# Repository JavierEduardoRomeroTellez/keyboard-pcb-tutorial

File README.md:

# keyboard-pcb-tutorial
Trying to make a keyboard PCB

I followed the guide of ai03, can find in the following link https://wiki.ai03.com/books/pcb-design/chapter/pcb-designer-guide

Here some screenshots

Schema:

PCB Routing:

3D view:

Note: In the KiCad rules check it throws me some errors but are about the footprints so i decided to ignore they, i dont really know if the PCB works

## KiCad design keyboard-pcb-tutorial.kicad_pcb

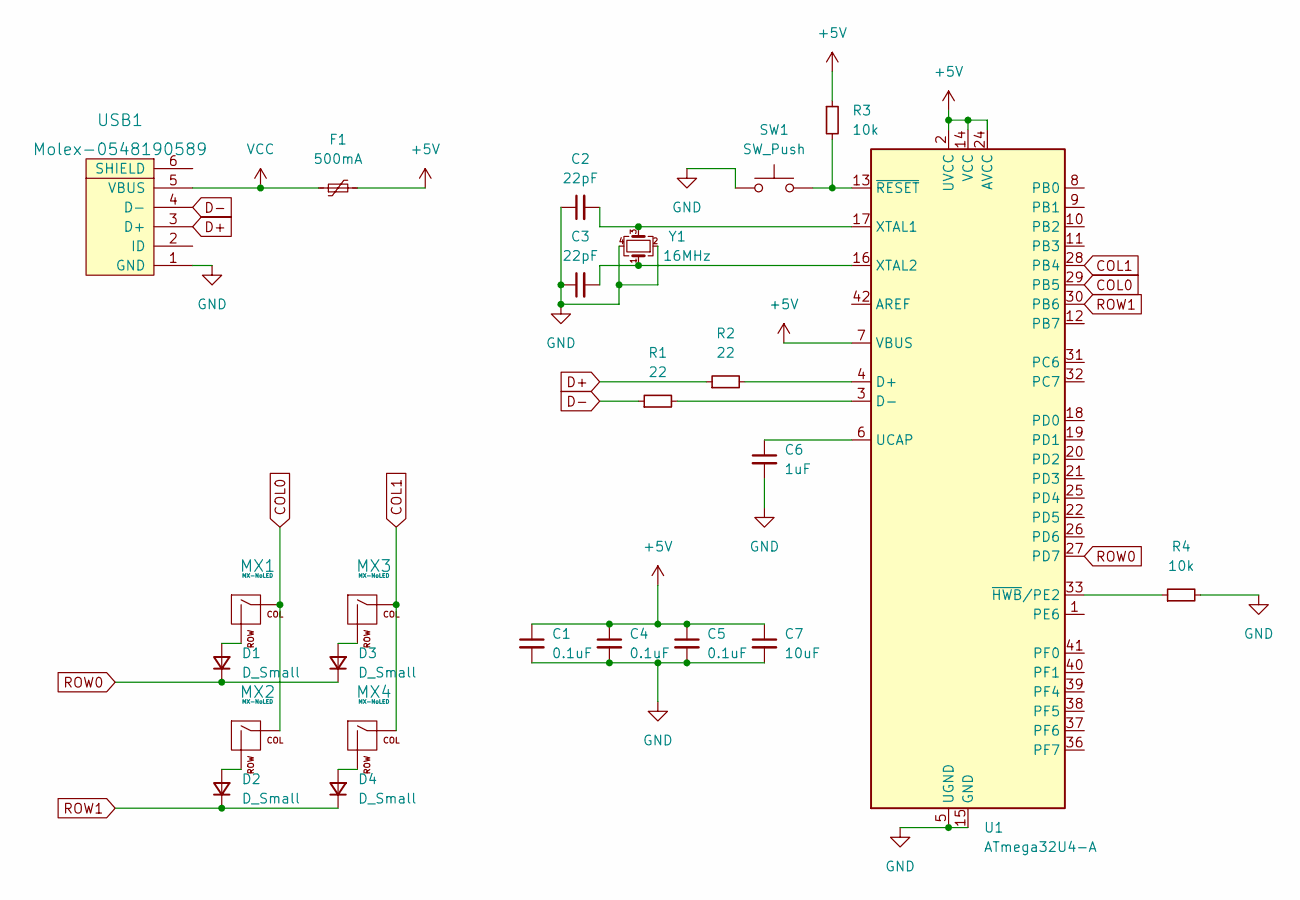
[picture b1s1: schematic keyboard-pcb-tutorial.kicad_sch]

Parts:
C1, C4, C5: 0.1uF; C_0805_2012Metric
C2, C3: 22pF; C_0805_2012Metric
C6: 1uF; C_0805_2012Metric
C7: 10uF; C_0805_2012Metric
D1, D2, D3, D4: D_Small; D_SOD-123
F1: 500mA; Fuse_1206_3216Metric
MX1, MX2, MX3, MX4: MX-NoLED; MX-1U-NoLED
R1, R2: 22; R_0805_2012Metric
R3, R4: 10k; R_0805_2012Metric
SW1: SW_Push; SKQG-1155865
U1: ATmega32U4-A; TQFP-44_10x10mm_P0.8mm
USB1: Molex-0548190589
Y1: 16MHz; Crystal_SMD_3225-4Pin_3.2x2.5mm

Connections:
+5V: C1.1, C4.1, C5.1, C7.1, F1.2, R3.1, U1.2 (UVCC), U1.7 (VBUS), U1.14 (VCC), U1.24 (AVCC), U1.34 (VCC), U1.44 (AVCC)
COL0: MX1.1 (COL), MX2.1 (COL), U1.29 (PB5)
COL1: MX3.1 (COL), MX4.1 (COL), U1.28 (PB4)
D+: R2.1, USB1.3 (D+)
D-: R1.1, USB1.4 (D-)
GND: C1.2, C2.1, C3.1, C4.2, C5.2, C6.2, C7.2, R4.2, SW1.1, U1.5 (UGND), U1.15 (GND), U1.23 (GND), U1.35 (GND), U1.43 (GND), USB1.1 (GND), Y1.2, Y1.4
unnamed: C2.2, U1.17 (XTAL1), Y1.3
unnamed: C3.2, U1.16 (XTAL2), Y1.1
unnamed: C6.1, U1.6 (UCAP)
unnamed: D1.2 (A), MX1.2 (ROW)
unnamed: D2.2 (A), MX2.2 (ROW)
unnamed: D3.2 (A), MX3.2 (ROW)
unnamed: D4.2 (A), MX4.2 (ROW)
unnamed: R1.2, U1.3 (D-)
unnamed: R2.2, U1.4 (D+)
unnamed: R3.2, SW1.2, U1.13 (~RESET)
unnamed: R4.1, U1.33 (~HWB/PE2)
ROW0: D1.1 (K), D3.1 (K), U1.27 (PD7)
ROW1: D2.1 (K), D4.1 (K), U1.30 (PB6)
VCC: F1.1, USB1.5 (VBUS)

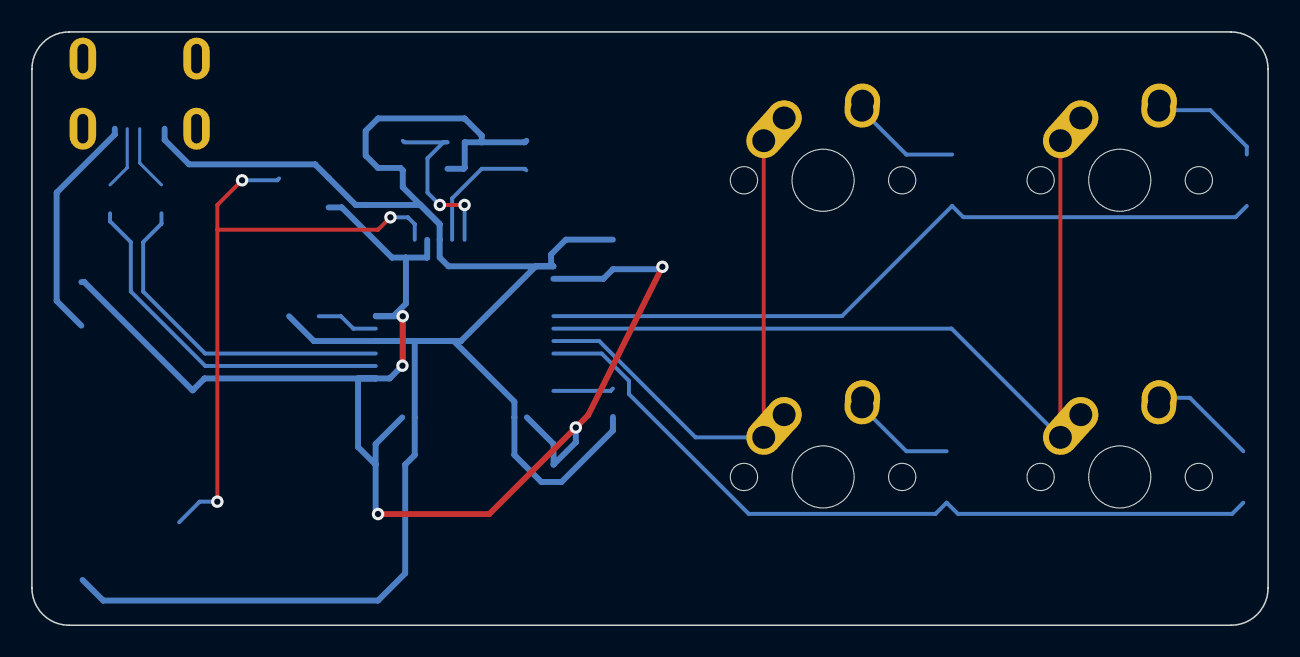
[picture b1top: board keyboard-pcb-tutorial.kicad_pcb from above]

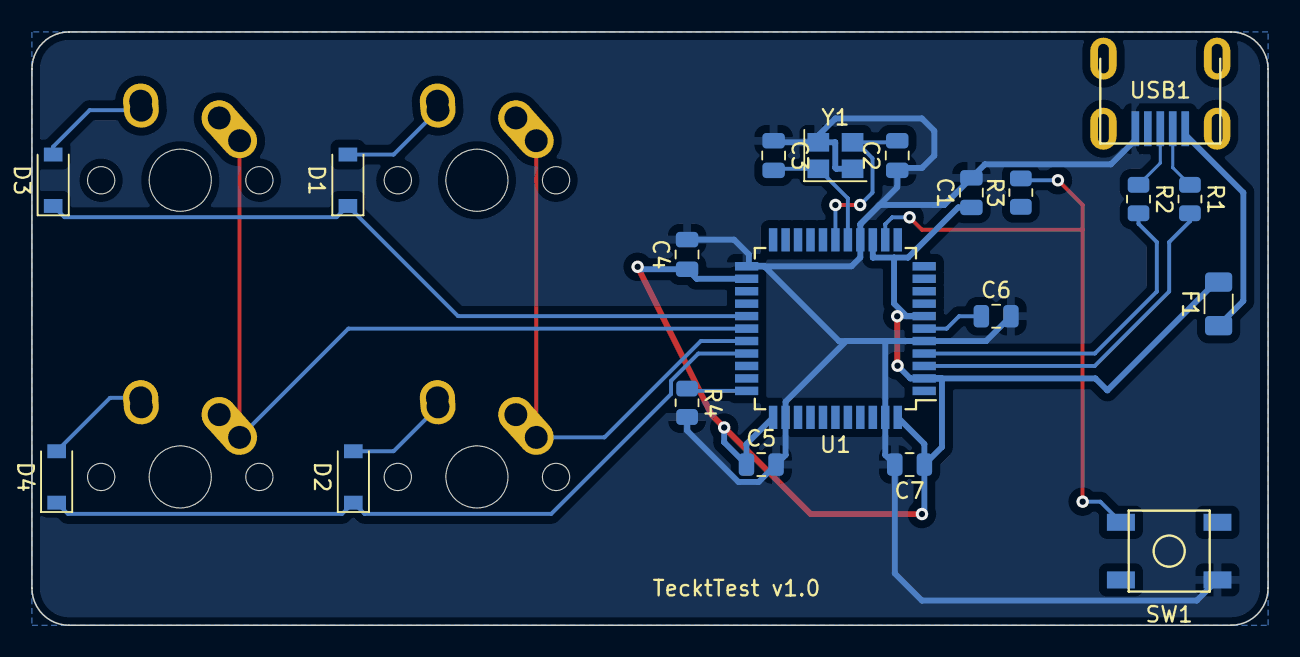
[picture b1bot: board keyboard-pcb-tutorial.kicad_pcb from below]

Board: 2 copper layers, 79.4 x 38.1 mm, 24 parts (20 on the bottom side), 20 nets.

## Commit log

2022-05-13 Created project files
2022-05-13 Add submodules
2022-05-13 Added libraries and footprints to project
2022-05-13 MCU schematic
2022-05-13 Added footprint bindings
2022-05-14 Placed the components on the PCB
2022-05-14 Added routing
2022-05-14 Finish the design
2022-05-14 Created gerber files
